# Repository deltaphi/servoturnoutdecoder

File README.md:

# Arudino Servo Decoder for the Motorola Protocol

* Motorola Input via INT0 (phase-correct)
* Control six Servos via the PWM outputs

# Dependencies

* Based on https://github.com/666c796e6e/LibMotorola/commit/a36dd47014a77b1eea2f04f38cabde1bba2f1c59
* Based on https://github.com/MicroBahner/MobaTools/commit/ad47b301049b6bf6d05046a2db197733567ed501

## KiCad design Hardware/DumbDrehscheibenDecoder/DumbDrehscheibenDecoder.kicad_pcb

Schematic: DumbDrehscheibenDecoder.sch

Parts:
A1: Arduino_Nano_v2.x; Arduino_Nano
C1: 470u; CP_Radial_D12.5mm_P5.00mm
D1, D2: D_Bridge_+-AA; Diode_Bridge_19.0x3.5x10.0mm_P5.0mm
D3: 1N4001; D_A-405_P7.62mm_Horizontal
H1, H2, H3, H4: MountingHole_Pad; MountingHole_3.2mm_M3_DIN965_Pad
J1, J2: Screw_Terminal_01x04; TerminalBlock_RND_205-00003_1x04_P5.00mm_Horizontal
R1, R3: 22k; R_Axial_DIN0204_L3.6mm_D1.6mm_P7.62mm_Horizontal
R2: 220; R_Axial_DIN0204_L3.6mm_D1.6mm_P7.62mm_Horizontal
SW1: SW_Push; SW_PUSH_6mm
U1: L293D; DIP-16_W7.62mm
U2: LTV-817; DIP-4_W7.62mm

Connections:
/MM_0: D1.4 (~~), D3.2, J2.2, U2.2
/MM_B: D1.3 (~~), J2.1, R1.2
/MM_Sense: A1.5 (D2), R2.1, U2.4
/MM_Vin: A1.30 (VIN), D1.1 (+)
/MOT_1Y: J1.4, U1.3
/MOT_2Y: J1.3, U1.6
/MOT_3Y: J1.1, U1.11
/MOT_4Y: J1.2, U1.14
/PWR_0: D2.4 (~~), J2.4
/PWR_B: D2.3 (~~), J2.3
/Pwr_Vin: D2.1 (+), U1.8
GND: A1.4 (GND), A1.29 (GND), C1.2, D1.2 (-), D2.2 (-), H1.1, H2.1, H3.1, H4.1, SW1.2, U1.4, U1.5, U1.12, U1.13, U2.3
unnamed: A1.6 (D3), U1.9
unnamed: A1.7 (D4), U1.7
unnamed: A1.8 (D5), U1.10
unnamed: A1.9 (D6), U1.1
unnamed: A1.10 (D7), U1.15
unnamed: A1.12 (D9), U1.2
unnamed: A1.19 (A0), R3.1, SW1.1
unnamed: D3.1, R1.1, U2.1
VCC: A1.27 (+5V), C1.1, R2.2, R3.2, U1.16

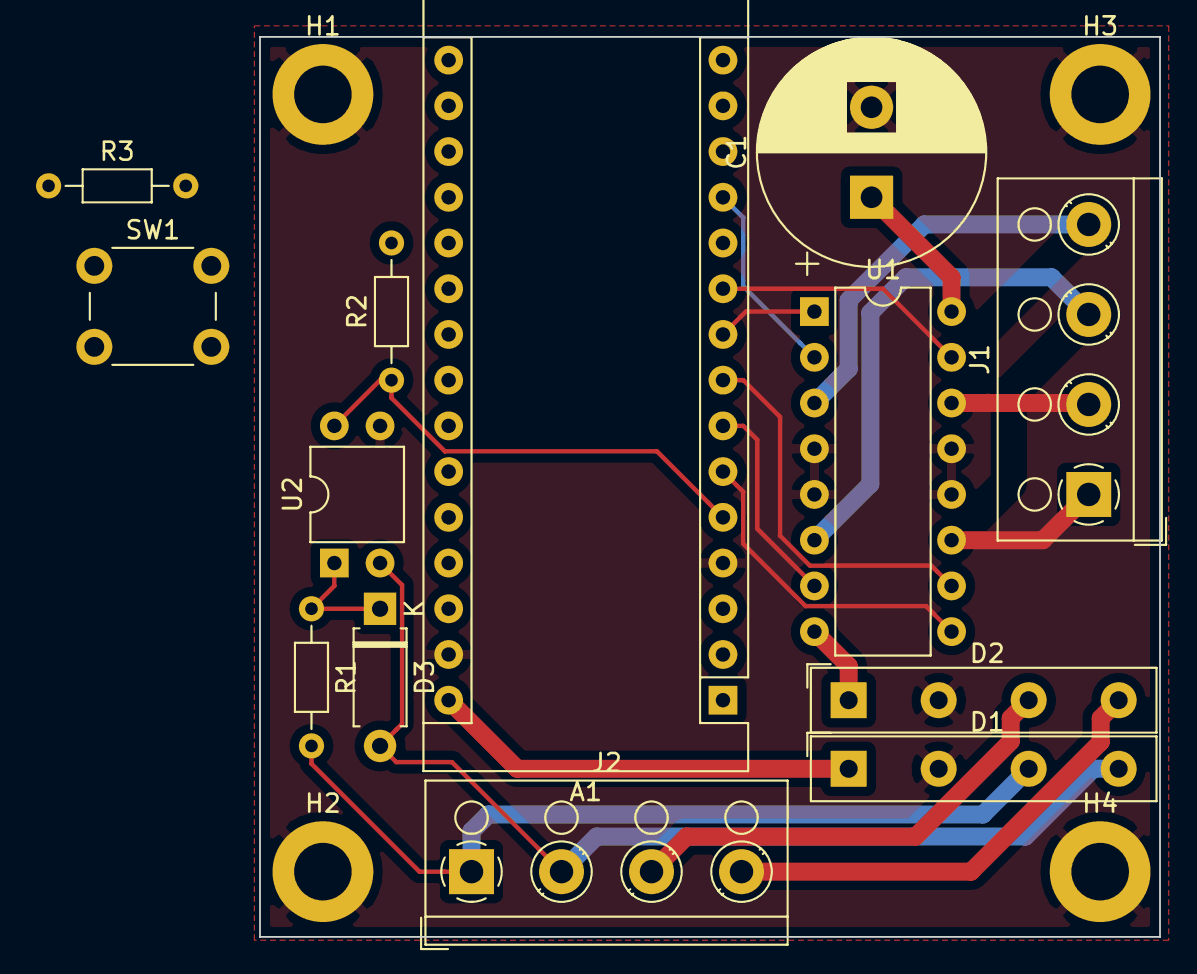
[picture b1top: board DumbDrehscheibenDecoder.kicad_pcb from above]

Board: 2 copper layers, 50.0 x 50.0 mm, 17 parts (0 on the bottom side), 21 nets.

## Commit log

2017-10-22 Added decoder and initial Servo test
2017-10-22 Added Dependency
2017-10-28 Upgrade to 6 Servos, new default values
2017-10-29 Updated settings
2017-10-29 Mostly working
2017-10-29 Version using MobaTools
2017-10-30 Further adjustments
2017-10-31 First board working
2017-10-31 Final final adjustments
2018-01-06 Initial work on the second Turnout board
2018-01-06 Adjusted Adresses and mechanics
2018-01-06 Adjusted values for left board
2018-01-13 Updated values after mechanical change
2019-12-01 Converted to PlatformIO project.
    Added referenced libraries as submodules.
2019-12-02 Extracted ExampleDataHandler to separate file
2019-12-02 Removed Servo functionality. Now 'polarization' only.
2019-12-02 Applied clang-format
2019-12-02 Configure serial speed
2019-12-02 Removed unused submodule
2019-12-03 Update .gitignore
    Now Supports KiCAD
2019-12-03 WIP: Initial version of PCB
2019-12-26 Added controller that works based on motor driver rather than relays
2019-12-26 Fixed some issues
2019-12-26 Updated the PCB
